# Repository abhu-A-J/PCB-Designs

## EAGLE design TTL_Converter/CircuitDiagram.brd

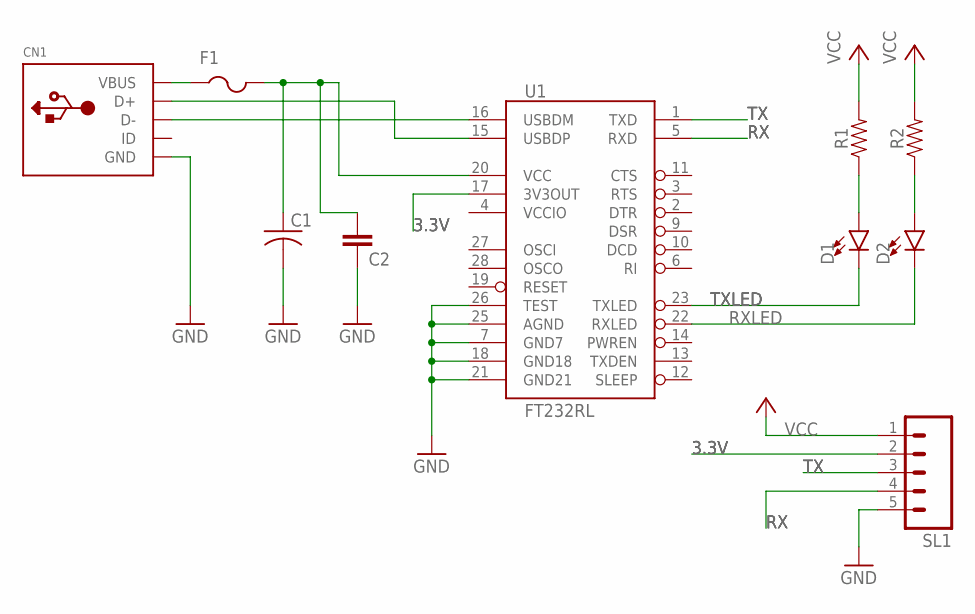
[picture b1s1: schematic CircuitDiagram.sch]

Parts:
C1: C-USC1206; C1206
C2: 1.0uF; 1206
CN1: USBMINIB; USB-MINIB
D1, D2: LED1206; LED-1206
F1: PTCFUSE-1206; R1206
R1, R2: 1206
SL1: M05; 05P
U1: FT232RL; SSOP28DB

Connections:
3.3V: SL1.2, U1.17 (3V3OUT)
GND: C1.2, C2.2, CN1.GND, SL1.5, U1.7 (GND7), U1.18 (GND18), U1.21 (GND21), U1.25 (AGND), U1.26 (TEST)
unnamed: CN1.VBUS, F1.1
unnamed: C1.1, C2.1, F1.2, U1.20 (VCC)
unnamed: CN1.D-, U1.16 (USBDM)
unnamed: CN1.D+, U1.15 (USBDP)
unnamed: D1.A, R1.1
unnamed: D2.A, R2.1
RX: SL1.4, U1.5 (RXD)
RXLED: D2.C, U1.22 (RXLED)
TX: SL1.3, U1.1 (TXD)
TXLED: D1.C, U1.23 (TXLED)
VCC: R1.2, R2.2, SL1.1
VCCIO: U1.4 (VCCIO)

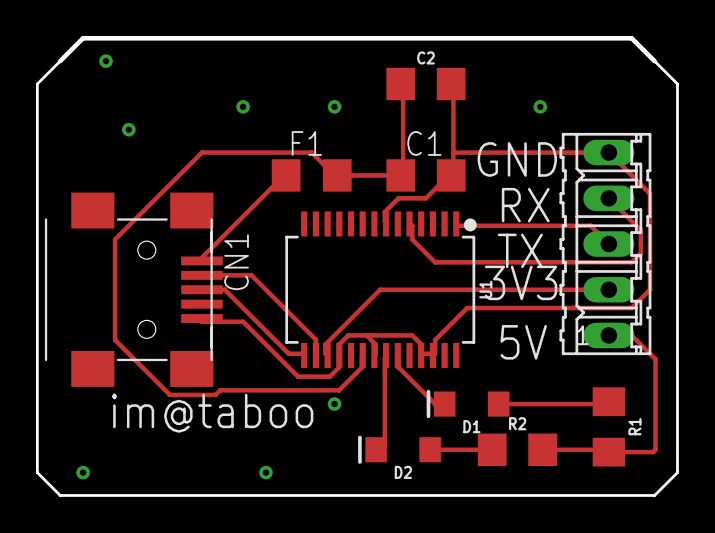
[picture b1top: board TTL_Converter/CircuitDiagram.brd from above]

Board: 2 copper layers, 35.5 x 25.3 mm, 10 parts (0 on the bottom side), 13 nets.

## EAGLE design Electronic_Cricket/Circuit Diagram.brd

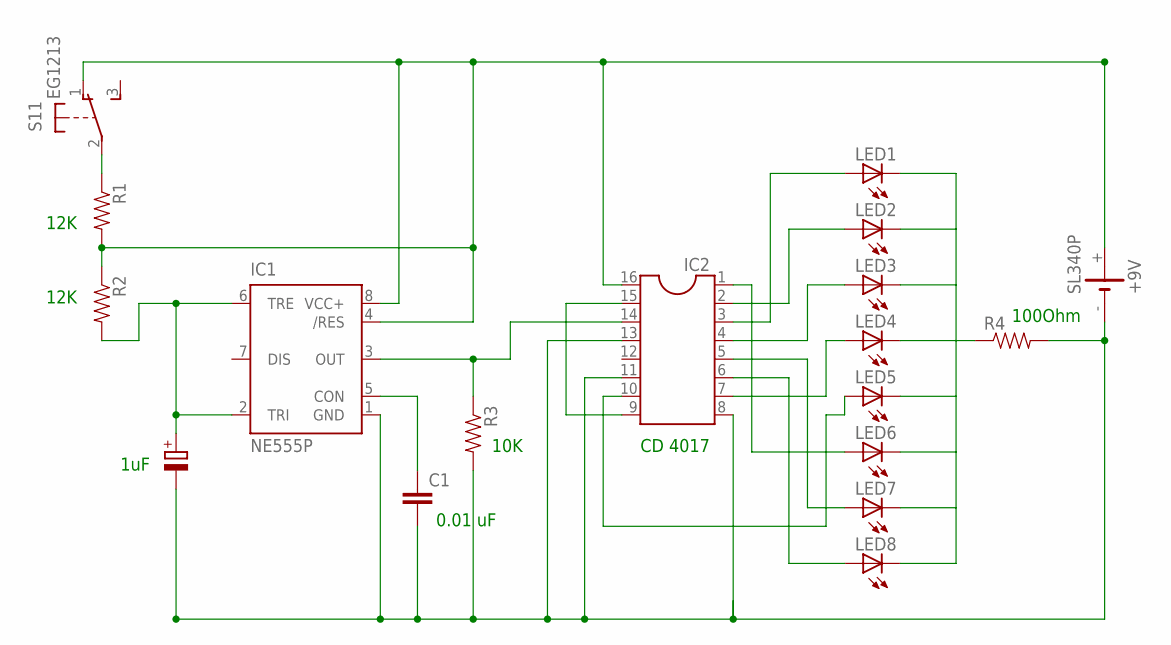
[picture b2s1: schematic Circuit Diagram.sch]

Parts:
+9V: SL340P; SL-340/P3.6V
C1: C2.5/6; C2.5-6
IC1: NE555P; DIL-08
IC2: DIL16
LED1, LED2, LED3, LED4, LED5, LED6, LED7, LED8: LEDB156; Q62902-B156
R1, R2, R3, R4: RESISTORAXIAL-0.3; AXIAL-0.3
S1: EG1213

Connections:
unnamed: IC2.3, LED1.A
unnamed: IC2.2, LED2.A
unnamed: IC2.4, LED3.A
unnamed: IC2.7, LED4.A
unnamed: IC2.10, LED5.A
unnamed: IC2.1, LED6.A
unnamed: IC2.5, LED7.A
unnamed: IC2.9, IC2.15
unnamed: +9V.-, C1.2, IC1.1 (GND), IC2.8, IC2.11, IC2.13, R3.P$2 (2), R4.P$2 (2)
unnamed: IC2.6, LED8.A
unnamed: R1.P$1 (1), S1.2
unnamed: LED1.K (C), LED2.K (C), LED3.K (C), LED4.K (C), LED5.K (C), LED6.K (C), LED7.K (C), LED8.K (C), R4.P$1 (1)
unnamed: IC1.3 (OUT), IC2.14, R3.P$1 (1)
unnamed: +9V.+, IC1.4 (/RES), IC1.8 (VCC+), IC2.16, R1.P$2 (2), R2.P$1 (1), S1.1 (O)
unnamed: IC1.2 (TRI), IC1.6 (TRE), R2.P$2 (2)
unnamed: C1.1, IC1.5 (CON)

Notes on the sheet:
12K
10K
100Ohm
1uF
0.01 uF
CD 4017

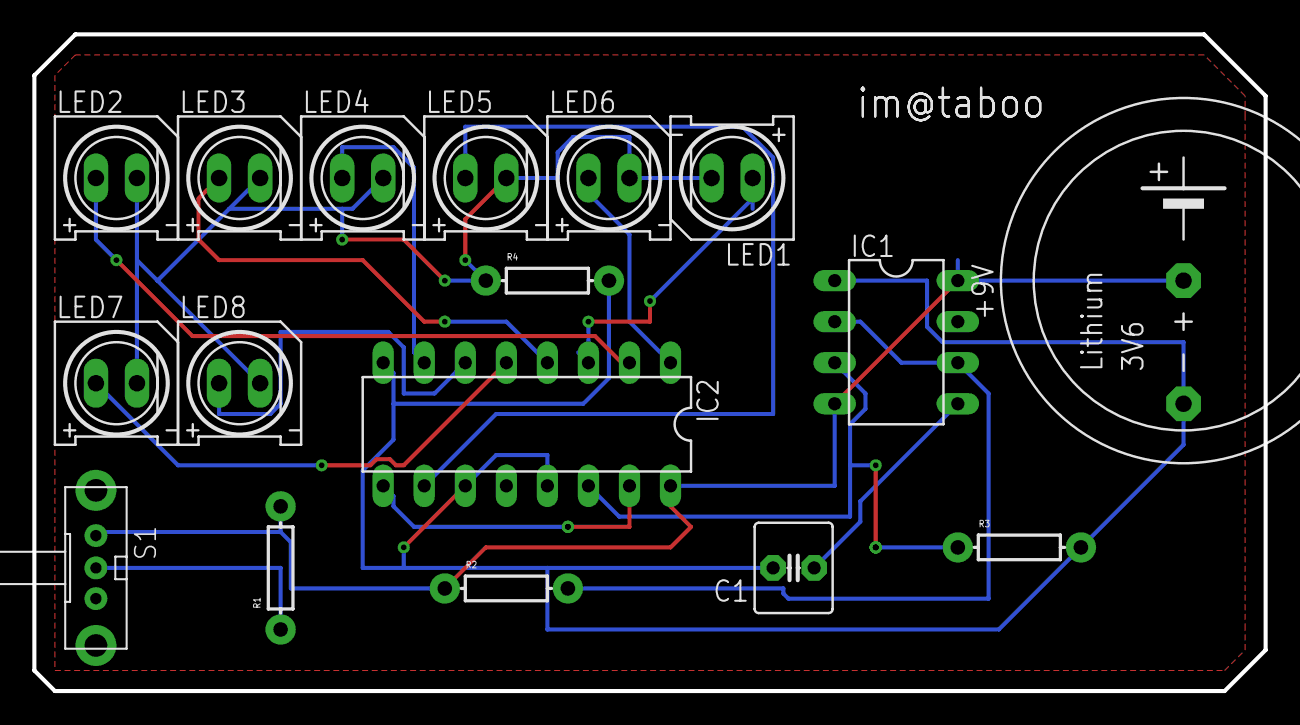
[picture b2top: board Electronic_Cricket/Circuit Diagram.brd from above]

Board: 2 copper layers, 76.2 x 40.6 mm, 17 parts (0 on the bottom side), 16 nets.

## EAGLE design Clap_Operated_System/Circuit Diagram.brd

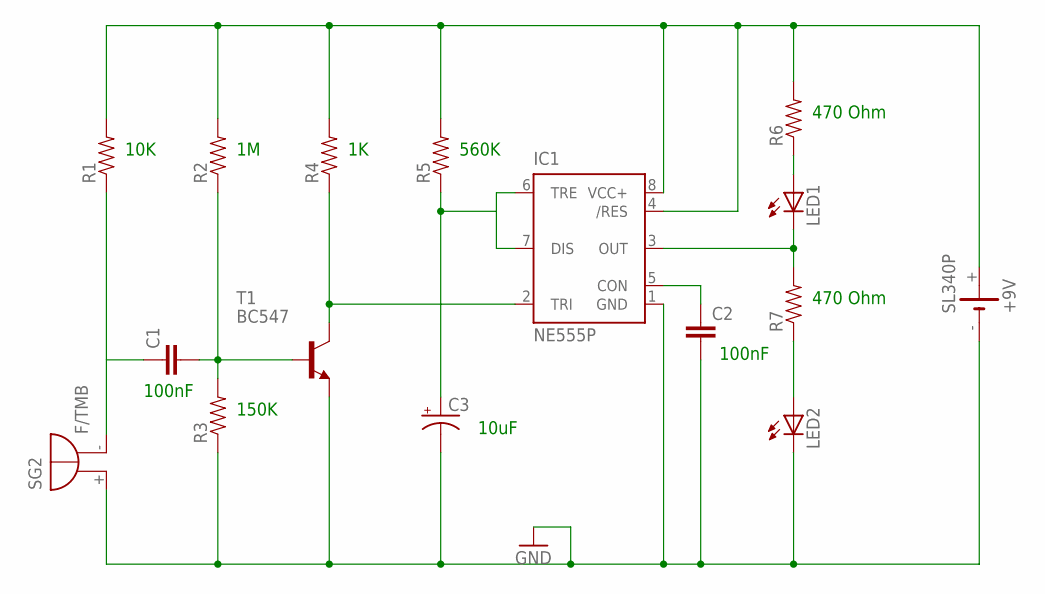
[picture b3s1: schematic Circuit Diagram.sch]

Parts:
+9V: SL340P; SL-340/P3.6V
C1, C2: 0.1UF-50V-20%(PTH)KIT-EZ; CAP-PTH-SMALL-KIT
C3: CAP_POLPTH1; CPOL-RADIAL-100UF-25V
IC1: NE555P; DIL-08
LED1, LED2: LED5MM
R1, R2, R3, R4, R5, R6, R7: 10KOHM1/6W5%(PTH)KIT; AXIAL-0.3-KIT
SG2: F/TMB
T1: BC547; TO92

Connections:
GND: +9V.-, C2.2, C3.2 (-), IC1.1 (GND), LED2.K (C), R3.P$1 (1), SG2.+, T1.1 (E)
unnamed: C1.1, R1.P$1 (1), SG2.-
unnamed: C1.2, R2.P$1 (1), R3.P$2 (2), T1.2 (B)
unnamed: IC1.2 (TRI), R4.P$1 (1), T1.3 (C)
unnamed: C3.1 (+), IC1.6 (TRE), IC1.7 (DIS), R5.P$1 (1)
unnamed: C2.1, IC1.5 (CON)
unnamed: IC1.3 (OUT), LED1.K (C), R7.P$2 (2)
unnamed: LED2.A, R7.P$1 (1)
unnamed: +9V.+, IC1.4 (/RES), IC1.8 (VCC+), R1.P$2 (2), R2.P$2 (2), R4.P$2 (2), R5.P$2 (2), R6.P$2 (2)
unnamed: LED1.A, R6.P$1 (1)

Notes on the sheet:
10K
150K
560K
470 Ohm
10uF
100nF

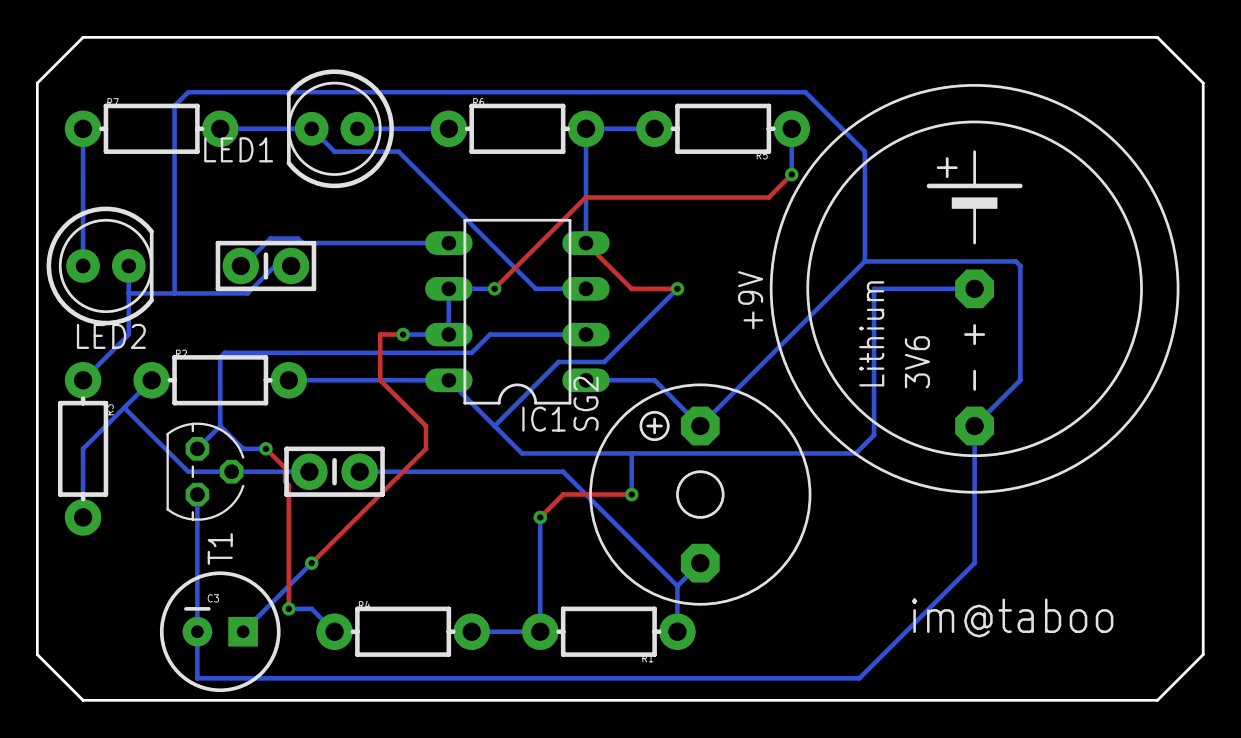
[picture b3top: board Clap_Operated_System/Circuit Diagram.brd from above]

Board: 2 copper layers, 64.8 x 36.8 mm, 16 parts (0 on the bottom side), 10 nets.

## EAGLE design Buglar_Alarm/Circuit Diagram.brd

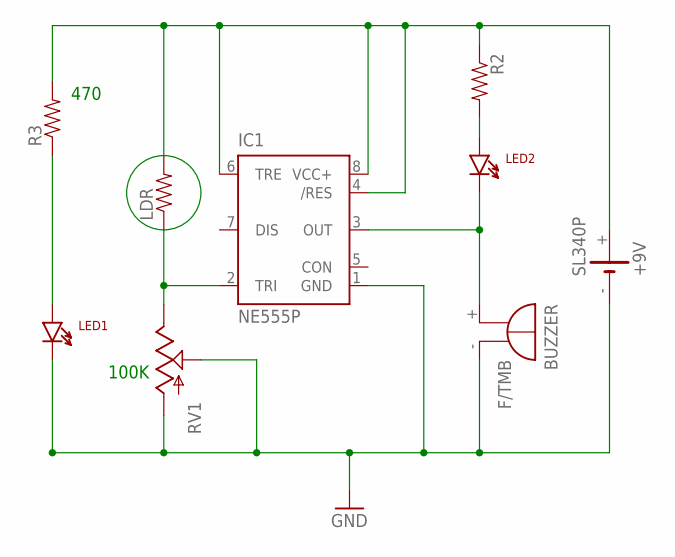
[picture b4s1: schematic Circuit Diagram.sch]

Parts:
+9V: SL340P; SL-340/P3.6V
BUZZER: F/TMB
IC1: NE555P; DIL-08
LDR: RESISTORAXIAL-0.3; AXIAL-0.3
LED1, LED2: LTE-302
R2, R3: RESISTORAXIAL-0.3; AXIAL-0.3
RV1: POTTRIM; TRIM_POT

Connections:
GND: +9V.-, BUZZER.-, IC1.1 (GND), LED1.C, RV1.1 (S), RV1.3 (A)
unnamed: IC1.2 (TRI), LDR.P$1 (1), RV1.2 (E)
unnamed: BUZZER.+, IC1.3 (OUT), LED2.C
unnamed: LED2.A, R2.P$2 (2)
unnamed: LED1.A, R3.P$1 (1)
unnamed: +9V.+, IC1.4 (/RES), IC1.6 (TRE), IC1.8 (VCC+), LDR.P$2 (2), R2.P$1 (1), R3.P$2 (2)

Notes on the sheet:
100K
470

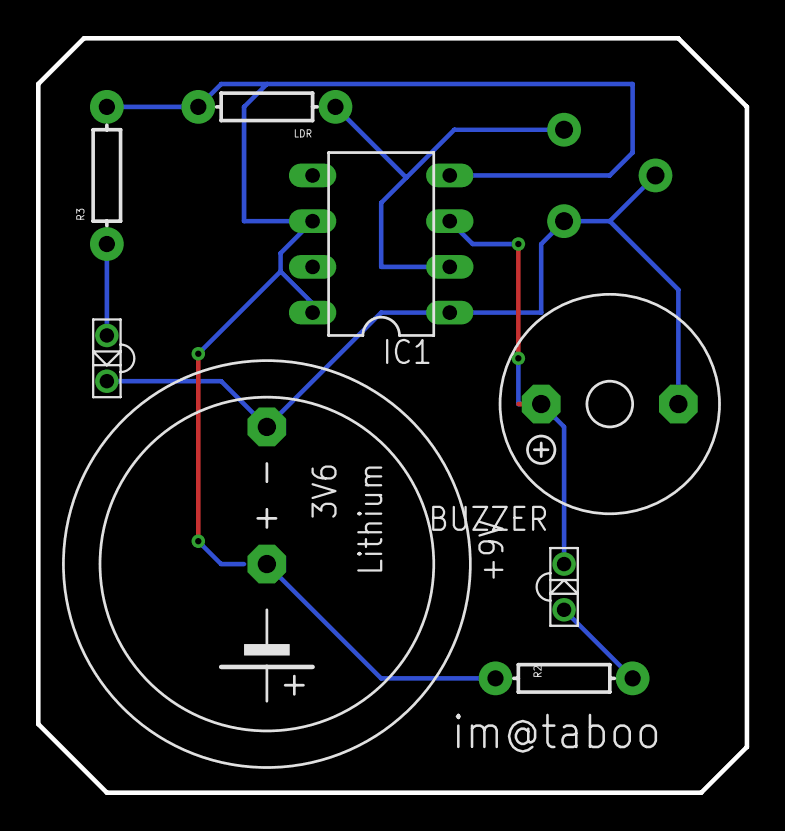
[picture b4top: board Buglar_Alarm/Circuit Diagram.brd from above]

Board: 2 copper layers, 39.4 x 41.9 mm, 9 parts (0 on the bottom side), 6 nets.

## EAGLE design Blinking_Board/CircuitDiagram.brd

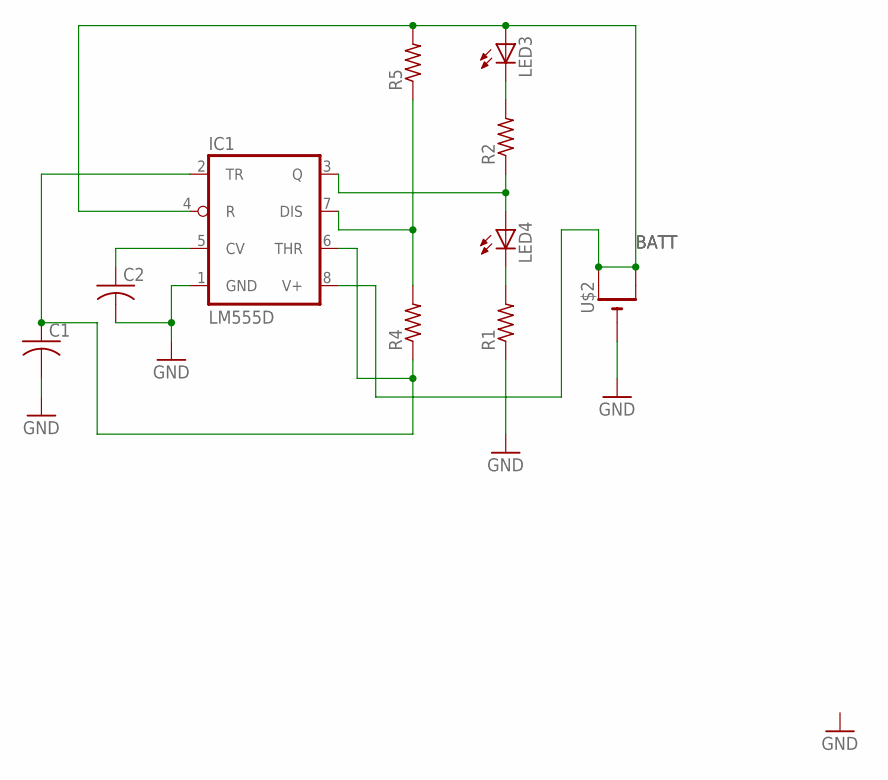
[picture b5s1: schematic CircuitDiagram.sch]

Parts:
C1, C2: C-USC0805; C0805
IC1: LM555D; SO08
LED3, LED4: LEDCHIP-LED0805; CHIP-LED0805
R1, R2, R4, R5: R-US_R0805; R0805
U$2: CR1220SMT; CR1220-SMD

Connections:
BATT: IC1.4 (R), IC1.8 (V+), LED3.A, R5.2, U$2.+$1 (+), U$2.+$2 (+1)
GND: C1.2, C2.2, IC1.1 (GND), R1.1, U$2.-
unnamed: LED4.C, R1.2
unnamed: IC1.3 (Q), LED4.A, R2.1
unnamed: LED3.C, R2.2
unnamed: IC1.7 (DIS), R4.2, R5.1
unnamed: C2.1, IC1.5 (CV)
unnamed: C1.1, IC1.2 (TR), IC1.6 (THR), R4.1

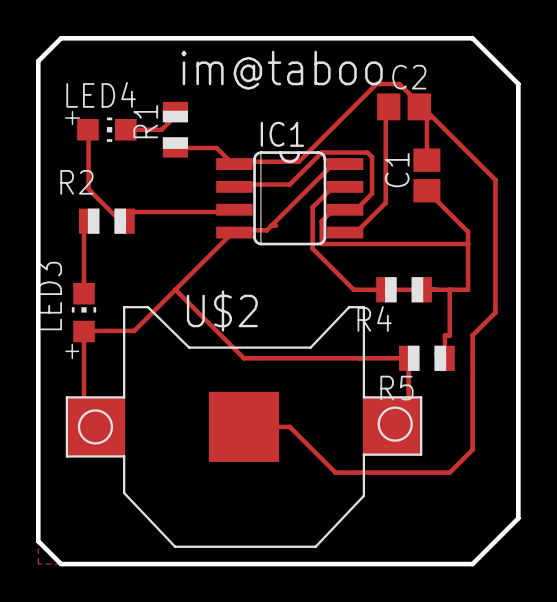
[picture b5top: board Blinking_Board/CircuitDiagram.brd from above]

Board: 2 copper layers, 26.7 x 29.2 mm, 10 parts (0 on the bottom side), 8 nets.

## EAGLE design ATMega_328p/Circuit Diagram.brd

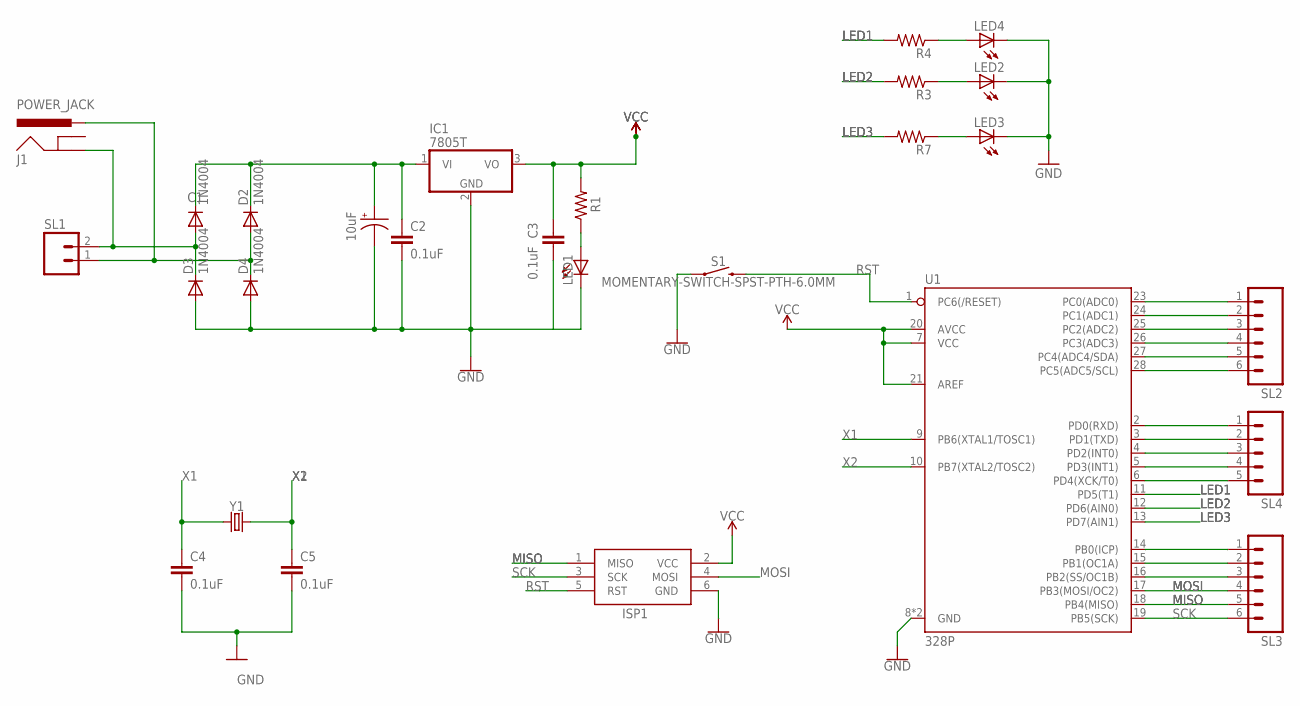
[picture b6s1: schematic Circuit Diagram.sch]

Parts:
C1: 10uF; CPOL-RADIAL-2.5MM-5MM
C2, C3, C4, C5: 0.1uF; CAP-PTH-SMALL-KIT
D1, D2, D3, D4: 1N4004; DO41-10
IC1: 7805T; TO220H
ISP1: AVRISP-6; AVRISP
J1: POWER_JACK; POWER_JACK_PTH
LED1, LED2, LED3, LED4: LED3MM
R1, R3, R4, R7: R-US_0207/9; 0207/9
S1: MOMENTARY-SWITCH-SPST-PTH-6.0MM; TACTILE_SWITCH_PTH_6.0MM
SL1: M02; 02P
SL2, SL3: M06; 06P
SL4: M05; 05P
U1: 328P; DIP28
Y1: CRYSTALPTH-HC49US; HC49US

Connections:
GND: C1.2 (-), C2.2, C3.2, C4.2, C5.2, D3.A, D4.A, IC1.2 (GND), ISP1.6 (GND), LED1.K (C), LED2.K (C), LED3.K (C), LED4.K (C), S1.1, U1.8 (GND), U1.22 (GND)
LED1: R4.2, U1.11 (PD5(T1))
LED2: R3.2, U1.12 (PD6(AIN0))
LED3: R7.2, U1.13 (PD7(AIN1))
MISO: ISP1.1 (MISO), SL3.5, U1.18 (PB4(MISO))
MOSI: ISP1.4 (MOSI), SL3.4, U1.17 (PB3(MOSI/OC2))
unnamed: LED4.A, R4.1
unnamed: C1.1 (+), C2.1, D1.C, D2.C, IC1.1 (VI)
unnamed: D1.A, D3.C, J1.GND, SL1.2
unnamed: SL2.1, U1.23 (PC0(ADC0))
unnamed: D2.A, D4.C, J1.PWR, SL1.1
unnamed: SL2.2, U1.24 (PC1(ADC1))
unnamed: LED1.A, R1.1
unnamed: SL2.3, U1.25 (PC2(ADC2))
unnamed: SL2.4, U1.26 (PC3(ADC3))
unnamed: SL2.5, U1.27 (PC4(ADC4/SDA))
unnamed: SL2.6, U1.28 (PC5(ADC5/SCL))
unnamed: SL4.1, U1.2 (PD0(RXD))
unnamed: SL4.2, U1.3 (PD1(TXD))
unnamed: SL4.3, U1.4 (PD2(INT0))
unnamed: SL4.4, U1.5 (PD3(INT1))
unnamed: SL4.5, U1.6 (PD4(XCK/T0))
unnamed: LED2.A, R3.1
unnamed: LED3.A, R7.1
unnamed: SL3.1, U1.14 (PB0(ICP))
unnamed: SL3.2, U1.15 (PB1(OC1A))
unnamed: SL3.3, U1.16 (PB2(SS/OC1B))
RST: ISP1.5 (RST), S1.3 (2), U1.1 (PC6(/RESET))
SCK: ISP1.3 (SCK), SL3.6, U1.19 (PB5(SCK))
VCC: C3.1, IC1.3 (VO), ISP1.2 (VCC), R1.2, U1.7 (VCC), U1.20 (AVCC), U1.21 (AREF)
X1: C4.1, U1.9 (PB6(XTAL1/TOSC1)), Y1.1
X2: C5.1, U1.10 (PB7(XTAL2/TOSC2)), Y1.2

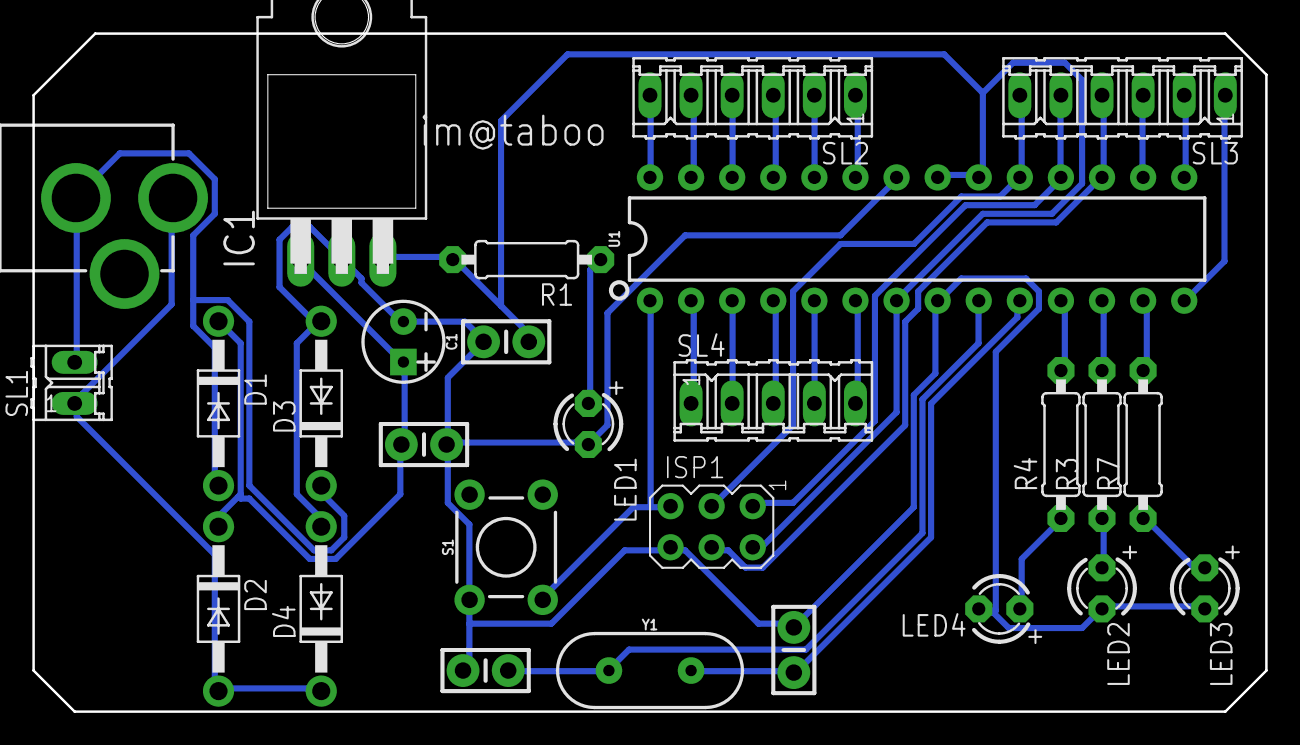
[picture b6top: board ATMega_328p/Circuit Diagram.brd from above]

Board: 2 copper layers, 76.2 x 41.9 mm, 27 parts (0 on the bottom side), 32 nets.

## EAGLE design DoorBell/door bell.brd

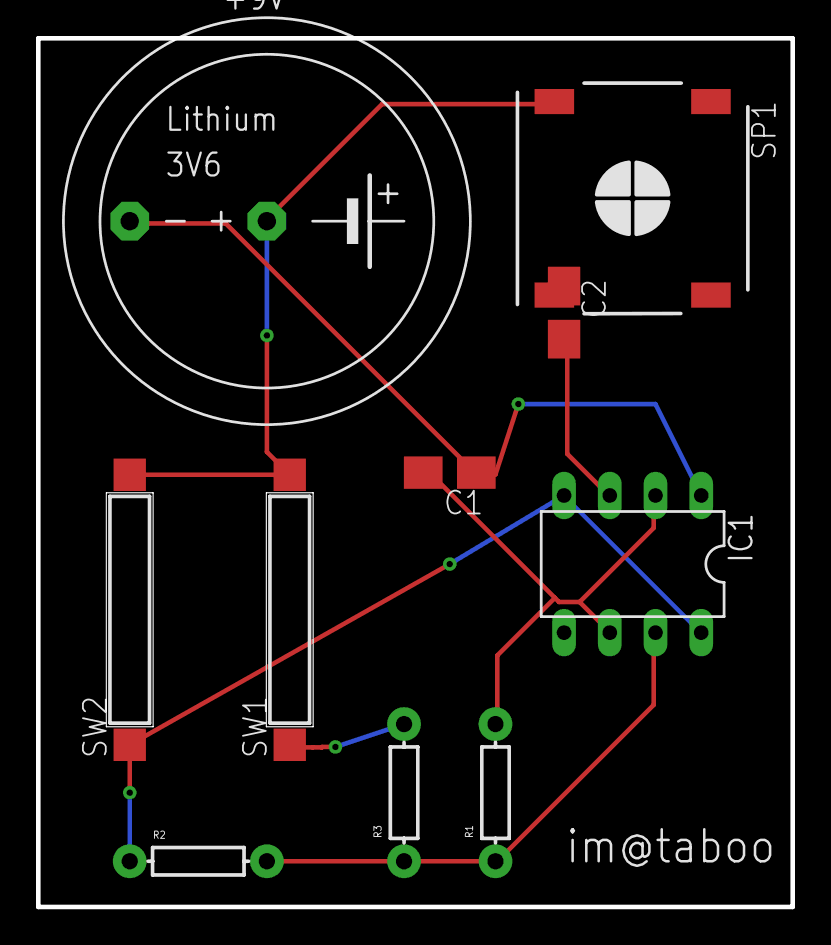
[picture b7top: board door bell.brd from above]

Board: 2 copper layers, 41.9 x 48.3 mm, 10 parts (0 on the bottom side), 8 nets.

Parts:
+9V: SL340P; SL-340/P3.6V
C1, C2: A/3216-18W
IC1: NE555P; DIL-08
R1, R2, R3: AXIAL-0.3
SP1: SMS-1308MS-2-R
SW1, SW2: CT10-XXXX-A2

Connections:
unnamed: C2.+, IC1.3
unnamed: C2.-, SP1.-
unnamed: C1.+, IC1.2, IC1.6, R1.P$2
unnamed: +9V.-, C1.-, IC1.1
unnamed: R3.P$2, SW1.1
unnamed: IC1.4, IC1.8, R2.P$1, SW2.1
unnamed: IC1.7, R1.P$1, R2.P$2, R3.P$1
unnamed: +9V.+, SP1.+, SW1.2, SW2.2

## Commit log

2019-04-17 5V Regulated Supply
2019-04-17 Microcontroller
2019-04-17 Timer based Pulse generator
2019-04-17 Alaram System
2019-04-17 Trigger System
2019-04-17 Door Bell Design
2019-04-17 Cricket Sound Circuit
2019-04-17 USB To TTL Converter

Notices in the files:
parts and their libraries:
SparkFun-Capacitors: Licensing: Creative Commons ShareAlike 4.0 International - https://creativecommons.org/licenses/by-sa/4.0
SparkFun-AnalogIC: Licensing: CC v3.0 Share-Alike You are welcome to use this library for commercial purposes.
